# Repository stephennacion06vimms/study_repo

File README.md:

# study_repo

My study repo notes, published as a local MkDocs site with the same look and
toolchain as VIMMS Engineering Docs.

## Read the notes

```powershell
.\scripts\docs.cmd          # live preview, opens http://127.0.0.1:8001
.\scripts\docs.cmd open     # strict build, then open site/index.html from disk
```

First run creates `tools\docs\.venv` (Python 3.13) and downloads the pinned
PlantUML jar (needs Java 11+). Details: `docs/writing-docs.md`.

## Layout

```text
docs/                      Notes (Markdown) -> the HTML site
  index.md                 Home page
  phono-360/roadmap.md     Phono 360 study roadmap
  sensors/ina226/          INA226 notes + datasheet
  lasers/                  Laser notes, images, datasheets
  electronics/, firmware/  Section pages pointing to the projects below
Electronics/               KiCad projects and manuals (kept in place for KiCad)
Firmware/                  nRF Connect / Zephyr study projects
mkdocs.yml                 Site config and navigation
tools/docs/                Pinned requirements + PlantUML build hook
scripts/docs.cmd|ps1       One-command launcher
.github/workflows/docs.yml Build-only CI check (mkdocs --strict)
```

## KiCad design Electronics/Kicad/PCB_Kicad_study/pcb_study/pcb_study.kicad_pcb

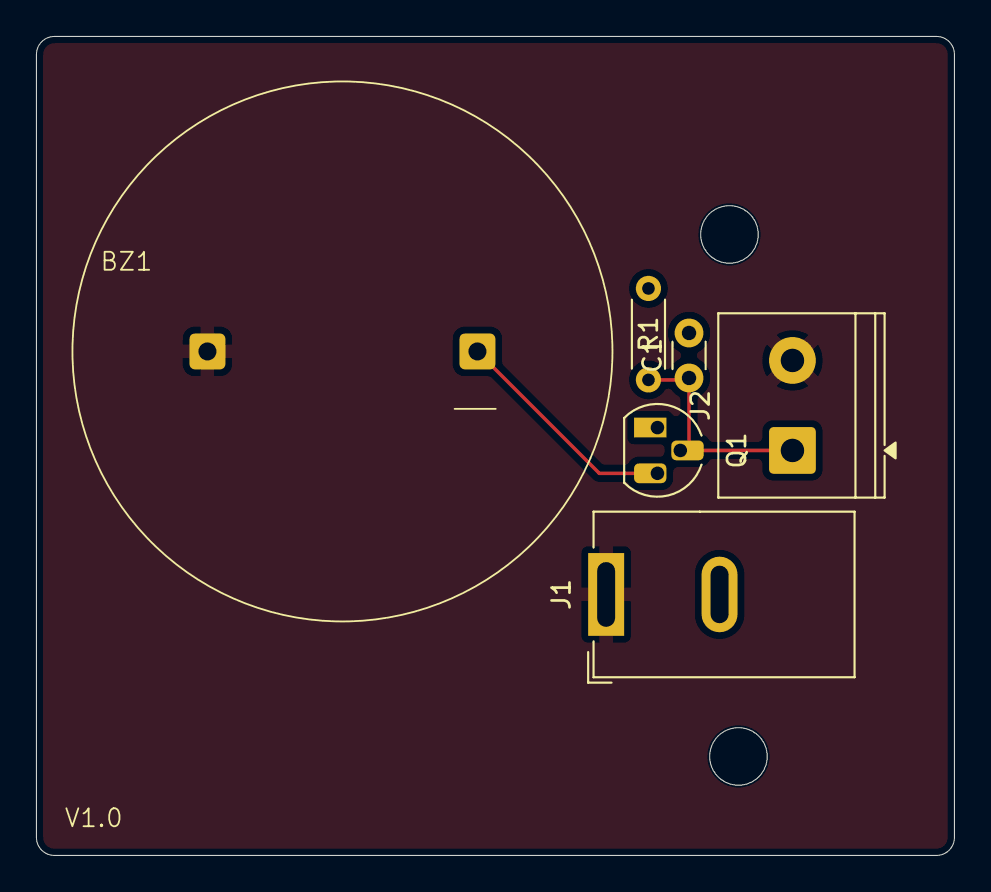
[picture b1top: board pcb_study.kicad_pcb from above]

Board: 2 copper layers, 51.0 x 45.5 mm, 6 parts (0 on the bottom side), 4 nets.

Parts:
BZ1: Buzzer; Buzzer_D30mm_H20mm_P15mm_688-1652-ND_AI-3035-TT-12V-R
C1: 1nF; C_Disc_D3.0mm_W1.6mm_P2.50mm
J1: Jack-DC; BarrelJack_GCT_DCJ200-10-A_Horizontal
J2: Screw_Terminal_01x02; TerminalBlock_Phoenix_PT-1,5-2-5.0-H_1x02_P5.00mm_Horizontal
Q1: 2N7000; TO-92_HandSolder
R1: 10M; R_Axial_DIN0204_L3.6mm_D1.6mm_P5.08mm_Horizontal

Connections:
/Gate: C1.1, J2.1, Q1.2 (G), R1.1
GND: C1.2, J1.2, Q1.1 (S), R1.2
unnamed: BZ1.2 (-), Q1.3 (D)
VCC: BZ1.1 (+), J1.1, J2.2
